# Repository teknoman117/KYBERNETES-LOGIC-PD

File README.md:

# Kybernetes 2 Logic Power Distribution Board

Power Distribution board for Kybernetes 2. Provides current monitoring and battery protection for a 3 cell LiPo battery and provides 5V via four USB-C ports.

Current monitoring IC is the INA219B and the switching regulator board is the Pololu D15V70F5S3. A open collector output is also provided to indicate low battery voltage.

### Assembled

### Switching Regulator Removed

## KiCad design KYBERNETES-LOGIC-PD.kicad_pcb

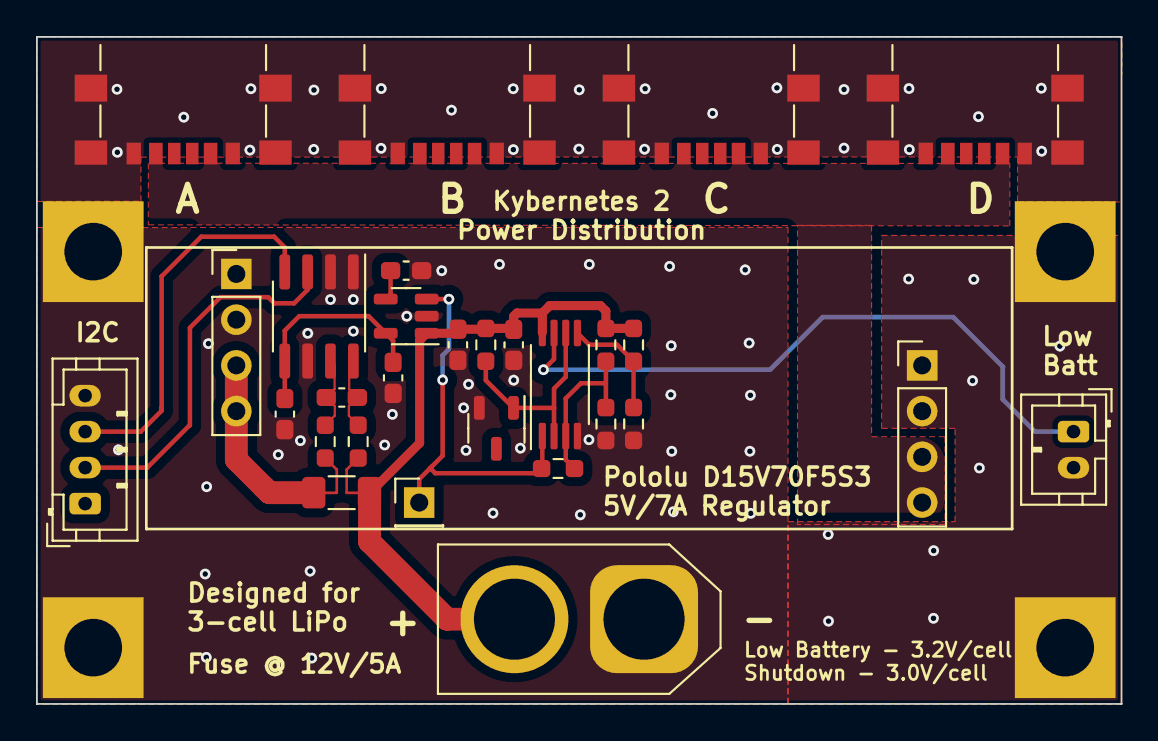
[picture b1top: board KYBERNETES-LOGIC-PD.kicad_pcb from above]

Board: 2 copper layers, 60.3 x 37.1 mm, 33 parts (0 on the bottom side), 15 nets.

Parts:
C1, C2: 100n; C_0603_1608Metric_Pad1.08x0.95mm_HandSolder
C3: 2.2u; C_0603_1608Metric_Pad1.08x0.95mm_HandSolder
C4: 10n; C_0603_1608Metric_Pad1.08x0.95mm_HandSolder
C5, C6: 1u; C_0603_1608Metric_Pad1.08x0.95mm_HandSolder
H1, H2, H3, H4: MountingHole_Pad; MountingHole_3.2mm_M3_Pad_Square
J1: Logic Battery; AMASS_XT60-M_1x02_P7.20mm_Vertical
J2: Regulator In; PinHeader_1x04_P2.54mm_Vertical
J3: Regulator Out; PinHeader_1x04_P2.54mm_Vertical
J4: Regulator Enable; PinHeader_1x01_P2.54mm_Vertical
J5: I2C; JST_PH_B4B-PH-K_1x04_P2.00mm_Vertical
J6, J7, J8, J9: USB_C_Receptacle_PowerOnly_6P; USB_C_Receptacle_GCT_USB4135-GF-A_6P_TopMnt_Horizontal
J10: Battery Low; JST_PH_B2B-PH-K_1x02_P2.00mm_Vertical
R1: 48k7; R_0603_1608Metric_Pad0.98x0.95mm_HandSolder
R2, R4: 22k1; R_0603_1608Metric_Pad0.98x0.95mm_HandSolder
R3: 44k2; R_0603_1608Metric_Pad0.98x0.95mm_HandSolder
R5: 1M; R_0603_1608Metric_Pad0.98x0.95mm_HandSolder
R6: 75k; R_0603_1608Metric_Pad0.98x0.95mm_HandSolder
R7: 8 mOhm; R_1206_3216Metric_Pad1.30x1.75mm_HandSolder
R8, R9: 10; R_0603_1608Metric_Pad0.98x0.95mm_HandSolder
U1: LM4040CEM3-3.0T; SOT-23-3
U2: LM2903; TSSOP-8_4.4x3mm_P0.65mm
U3: INA219BxD; SOIC-8_3.9x4.9mm_P1.27mm
U4: LP2985-3.3; SOT-23-5

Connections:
+3V3: C2.1, C3.1, U3.5 (VS), U4.5 (VOUT)
+5V: J3.3, J3.4, J6.A9 (VBUS), J6.B9 (VBUS), J7.A9 (VBUS), J7.B9 (VBUS), J8.A9 (VBUS), J8.B9 (VBUS), J9.A9 (VBUS), J9.B9 (VBUS)
+12V: C1.1, C6.1, J1.2, R1.1, R3.1, R6.1, R7.1, R8.1, U2.8 (V+), U4.1 (VIN)
GND: C1.2, C2.2, C3.2, C4.2, C6.2, H1.1, H2.1, H3.1, H4.1, J1.1, J2.1, J2.2, J3.1, J3.2, J5.4, J6.A12 (GND), J6.B12 (GND), J6.S1 (SHIELD), J7.A12 (GND), J7.B12 (GND), J7.S1 (SHIELD), J8.A12 (GND), J8.B12 (GND), J8.S1 (SHIELD), J9.A12 (GND), J9.B12 (GND), J9.S1 (SHIELD), J10.2, R2.2, R4.2, U1.2 (A), U2.4 (V-), U3.1 (A1), U3.2 (A0), U3.6 (GND), U4.2 (GND)
LogicBattCritSense: R3.2, R4.1, R5.1, U2.3 (+)
LogicBattLowSense: R1.2, R2.1, U2.5 (+)
LogicBattRef: R6.2, U1.1 (K), U2.2 (-), U2.6 (-)
unnamed: J10.1, U2.7
unnamed: C5.1, R8.2, U3.8 (IN+)
unnamed: C5.2, R9.2, U3.7 (IN-)
unnamed: C4.1, U4.4 (BP)
REGULATOR_EN: J4.1, R5.2, U2.1, U4.3 (ON/~OFF)
REGULATOR_IN: J2.3, J2.4, R7.2, R9.1
SCL: J5.3, U3.4 (SCL)
SDA: J5.2, U3.3 (SDA)

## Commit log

2023-03-02 further work
2023-03-02 more work
2023-03-02 derp
2023-03-02 first version for manufacturing
2023-03-03 source needs 10 Kohm pullups to advertise 3A capability
2024-08-16 add readme and license
2024-08-16 add schematic rendering
